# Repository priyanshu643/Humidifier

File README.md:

# DIY Humidifier Project with Custom PCB

Welcome to the repository for my DIY Humidifier project! This project aims to create a functional and efficient humidifier, featuring a custom-designed Printed Circuit Board (PCB) to integrate all components neatly.

I, Priyanshu, personally designed the custom PCB for this project, focusing on creating a compact and tailored solution for this humidifier.

**documentation** https://docs.google.com/document/d/1Now5aLwraL7LMPHntZHk1pkwH7MLB5T6pkGFi95Vkyw/edit?usp=sharing

## ✨ Features
*   Automated humidity control (potentially using a DHT sensor or similar).
*   Compact design thanks to the custom PCB.
*   (Add more specific features as your project develops, e.g., display, user controls, mist level adjustment).
*   Reliable operation due to integrated components.

## 🛠️ Hardware Components (Example - update with your actuals)
*   **Microcontroller:** (e.g., ESP32, ESP8266, Arduino Nano)
*   **Humidity Sensor:** (e.g., DHT11, DHT22, SHT31)
*   **Atomizer/Mist Maker Module:**
*   **Power Supply:** (e.g., 5V USB, dedicated power module)
*   **Control Circuitry:** (e.g., MOSFET or Relay to drive the atomizer)
*   **Custom PCB:** Designed by me ([Priyanshu](https://github.com/priyanshu643)).

## 🔌 PCB Design
The core of this project is the custom PCB, designed by me ([Priyanshu](https://github.com/priyanshu643)). This board was developed to:
*   Minimize wiring and potential connection issues.
*   Provide a stable platform for all electronic components.
*   Achieve a compact form factor.

## (Software)
The firmware (likely Arduino C/C++ ) for controlling the humidifier can be found in the `/firmware` or `/src` directory. It handles:
*   Implementing the control logic for humidity regulation.
*   (Potentially) Interfacing with pushbuttons.

## 🚀 Getting Started (To be detailed)
1.  Clone this repository: `git clone https://github.com/priyanshu643/Humidifier.git`
2.  Gather all necessary hardware components.
3.  Solder the components onto the PCB.
4.  Upload the firmware from the `/firmware` directory to the microcontroller.
5.  Assemble the humidifier unit.
6.  Test and calibrate!

## 📚 Further Reading & Resources
To gain more knowledge on the topics involved in this project, consider exploring documentation and tutorials related to:
*   **Microcontroller Programming:** (e.g., Arduino Reference).
*   **Humidity Sensors:**
*   **PCB Design Basics:** Tutorials for your chosen EDA software (e.g., KiCad).
*   **Soldering Techniques:** Guides for through-hole and SMD soldering.
*   **else** every another required documents are presented in document: https://docs.google.com/document/d/1Now5aLwraL7LMPHntZHk1pkwH7MLB5T6pkGFi95Vkyw/edit?usp=sharing

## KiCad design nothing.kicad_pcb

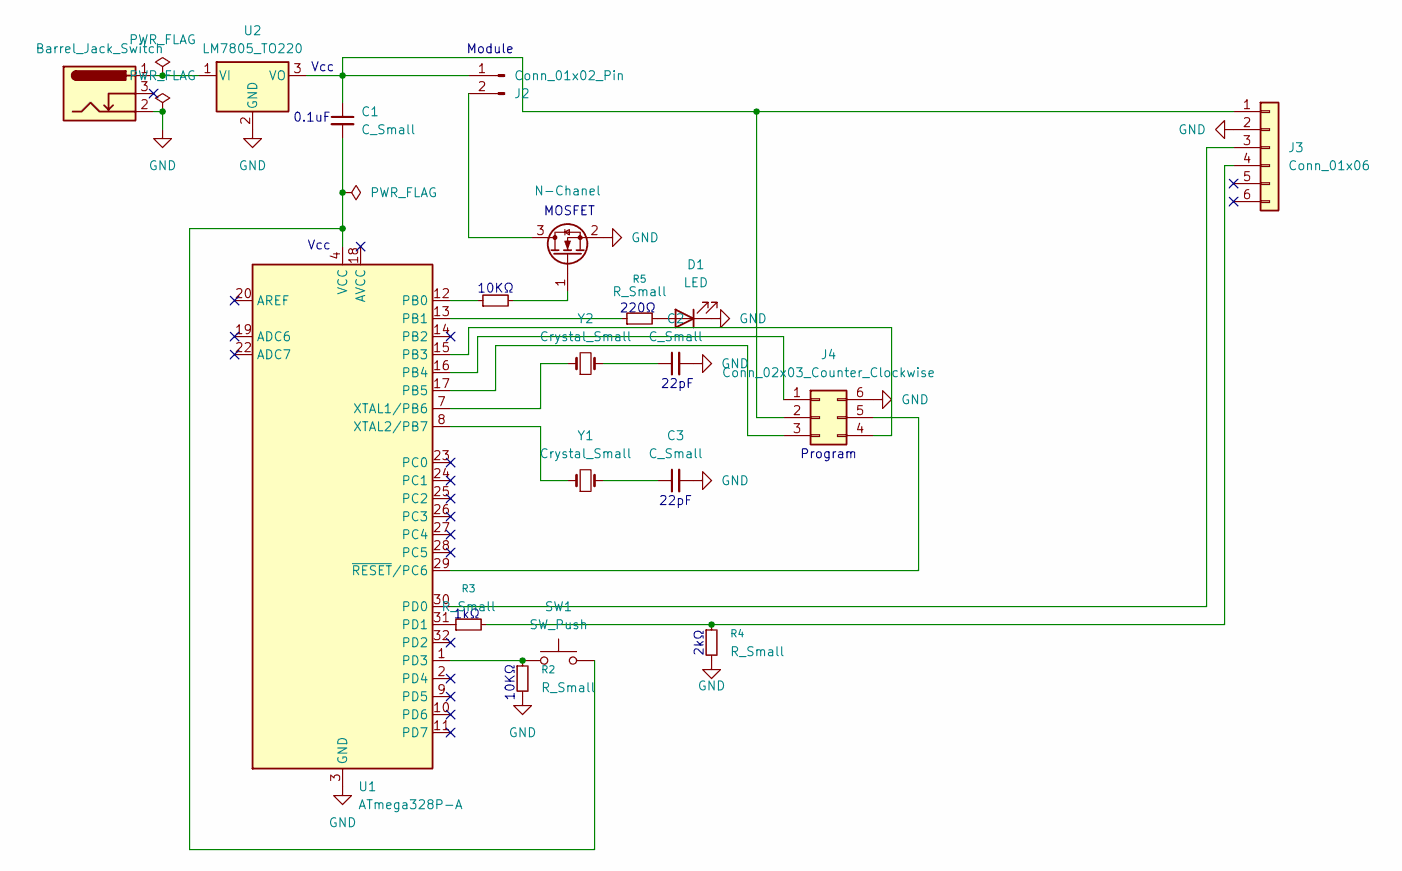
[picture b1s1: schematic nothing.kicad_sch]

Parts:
C1, C2, C3: C_Small; C_Disc_D3.0mm_W1.6mm_P2.50mm
D1: LED; LED_D5.0mm
J2: Conn_01x02_Pin; PinHeader_1x02_P2.54mm_Vertical
J3: Conn_01x06; PinHeader_1x06_P2.54mm_Vertical
J4: Conn_02x03_Counter_Clockwise; PinHeader_2x03_P2.54mm_Vertical
J5: Barrel_Jack_Switch; BarrelJack_Horizontal
Q1: N-Chanel; TO-220-3_Vertical
R1, R2, R3, R4, R5: R_Small; R_Axial_DIN0207_L6.3mm_D2.5mm_P10.16mm_Horizontal
SW1: SW_Push; SW_PUSH_6mm
U1: ATmega328P-A; TQFP-32_7x7mm_P0.8mm
U2: LM7805_TO220; TO-220-3_Vertical
Y1, Y2: Crystal_Small; Crystal_HC49-U_Vertical

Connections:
GND: C2.2, C3.2, D1.1 (K), J3.2, J4.6, J5.2, Q1.2 (S), R2.2, R4.2, U1.3 (GND), U1.5 (GND), U1.21 (GND), U2.2 (GND)
unnamed: C1.2, SW1.2, U1.4 (VCC), U1.6 (VCC)
unnamed: C2.1, Y2.2
unnamed: C3.1, Y1.2
unnamed: D1.2 (A), R5.2
unnamed: C1.1, J2.1, J3.1, J4.2, U2.3 (VO)
unnamed: J2.2, Q1.3 (D)
unnamed: J3.3, U1.30 (PD0)
unnamed: J3.4, R3.2, R4.1
unnamed: J4.1, U1.16 (PB4)
unnamed: J4.3, U1.17 (PB5)
unnamed: J4.4, U1.15 (PB3)
unnamed: J4.5, U1.29 (~RESET/PC6)
unnamed: Q1.1 (G), R1.2
unnamed: R1.1, U1.12 (PB0)
unnamed: R5.1, U1.13 (PB1)
unnamed: R3.1, U1.31 (PD1)
unnamed: R2.1, SW1.1, U1.1 (PD3)
unnamed: U1.7 (XTAL1/PB6), Y2.1
unnamed: U1.8 (XTAL2/PB7), Y1.1
unnamed: J5.1, U2.1 (VI)

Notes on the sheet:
10KΩ
Program
2kΩ
1kΩ
MOSFET
0.1uF
Vcc
Module
22pF
220Ω

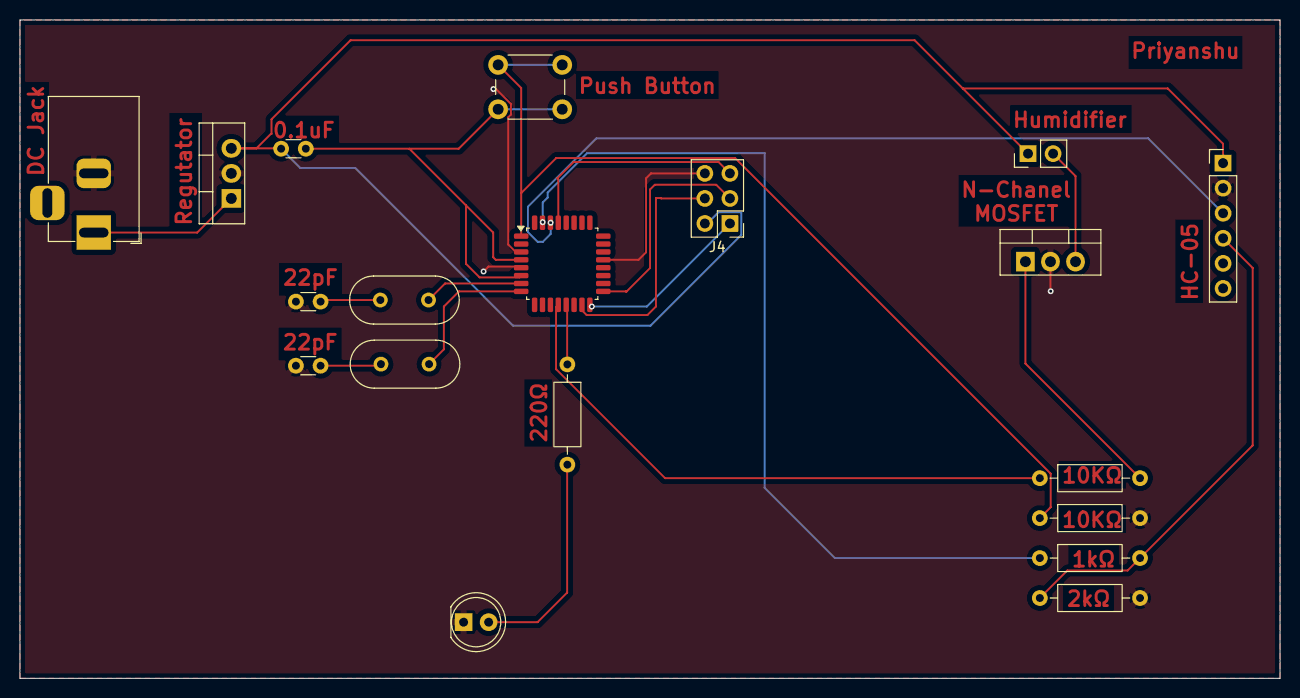
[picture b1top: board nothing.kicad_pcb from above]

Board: 2 copper layers, 127.8 x 66.8 mm, 19 parts (0 on the bottom side), 21 nets.

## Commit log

2025-05-25 Update README.md
    adding essintial
